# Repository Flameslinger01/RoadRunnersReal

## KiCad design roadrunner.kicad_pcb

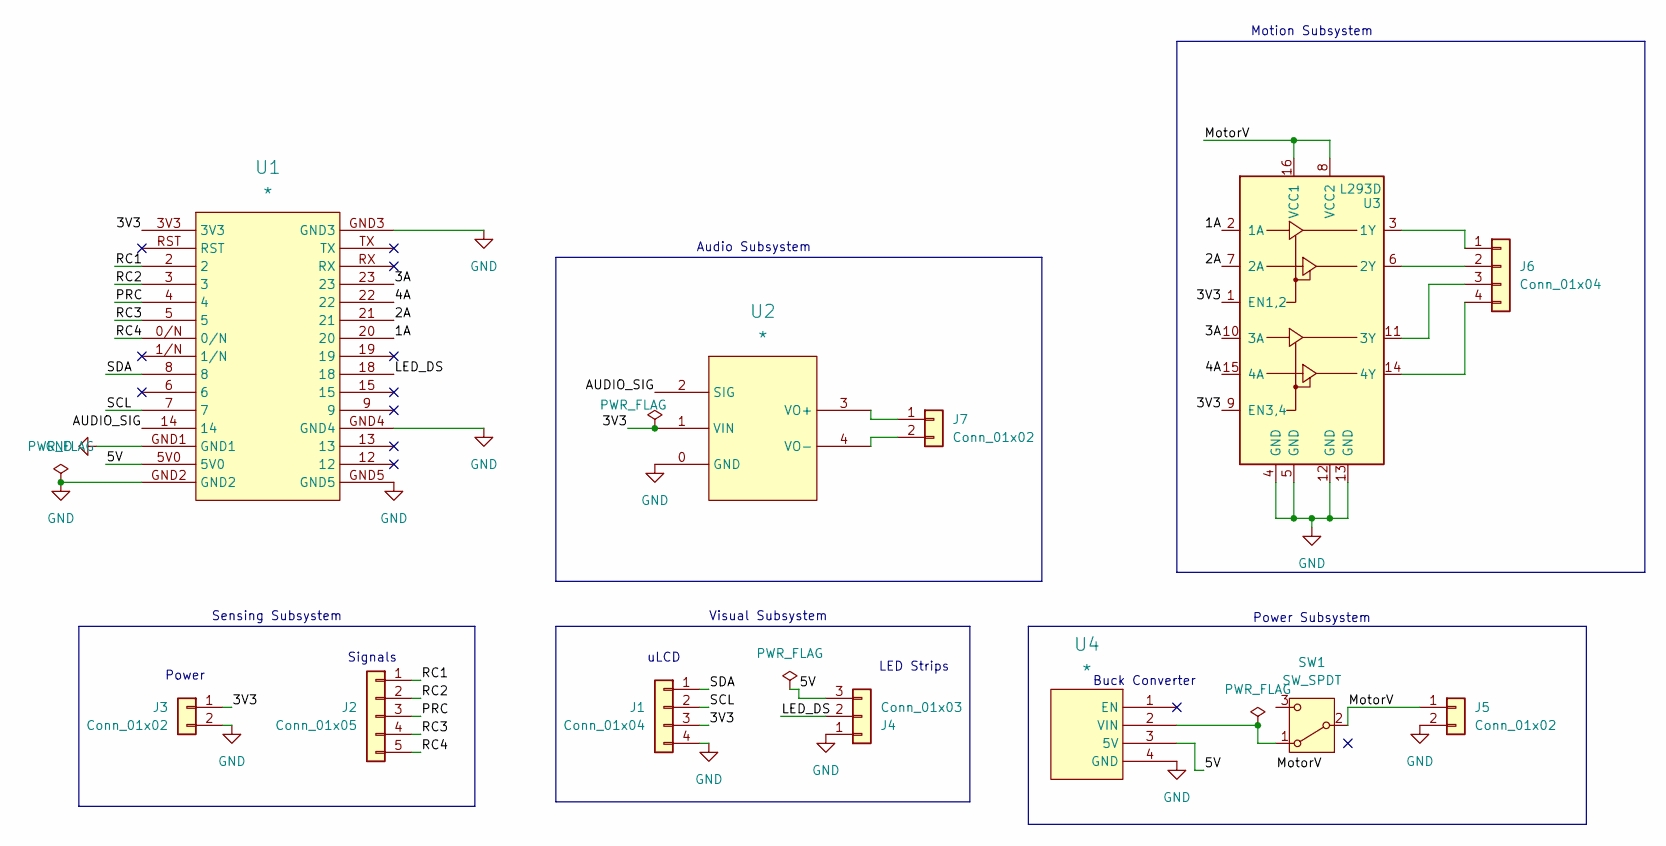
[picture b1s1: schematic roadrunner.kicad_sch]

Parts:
J1, J6: Conn_01x04; JST_XH_B4B-XH-A_1x04_P2.50mm_Vertical
J2: Conn_01x05; JST_XH_B5B-XH-A_1x05_P2.50mm_Vertical
J3, J5, J7: Conn_01x02; JST_XH_B2B-XH-A_1x02_P2.50mm_Vertical
J4: Conn_01x03; JST_XH_B3B-XH-A_1x03_P2.50mm_Vertical
SW1: SW_SPDT; SW_Slide-03_Wuerth-WS-SLTV_10x2.5x6.4_P2.54mm
U1: *; ESP32
U2: *; Adafruit_PAM8904
U3: L293D; DIP-16_W7.62mm
U4: *; ADA4683_MPM3610_BREAKOUT

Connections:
/1A: U1.20, U3.2 (1A)
/2A: U1.21, U3.7 (2A)
/3A: U1.23, U3.10 (3A)
/3V3: J1.3, J3.1, U1.3V3, U2.1 (VIN), U3.1 (EN1,2), U3.9 (EN3,4)
/4A: U1.22, U3.15 (4A)
/5V: J4.3, U1.5V0, U4.3 (5V)
/AUDIO_SIG: U1.14, U2.2 (SIG)
/LED_DS: J4.2, U1.18
/MotorV: J5.1, SW1.2 (B), U3.8 (VCC2), U3.16 (VCC1)
/PRC: J2.3, U1.4
/RC1: J2.1, U1.2
/RC2: J2.2, U1.3
/RC3: J2.4, U1.5
/RC4: J2.5, U1.0/N
/SCL: J1.2, U1.7
/SDA: J1.1, U1.8
GND: J1.4, J3.2, J4.1, J5.2, U1.GND1, U1.GND2, U1.GND3, U1.GND4, U1.GND5, U2.0 (GND), U3.4 (GND), U3.5 (GND), U3.12 (GND), U3.13 (GND), U4.4 (GND)
unnamed: J6.1, U3.3 (1Y)
unnamed: J6.2, U3.6 (2Y)
unnamed: J6.3, U3.11 (3Y)
unnamed: J6.4, U3.14 (4Y)
unnamed: J7.1, U2.3 (VO+)
unnamed: J7.2, U2.4 (VO-)
unnamed: SW1.1 (A), U4.2 (VIN)

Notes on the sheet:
Signals
Buck Converter
Audio Subsystem
uLCD
Power
Visual Subsystem
Power Subsystem
LED Strips
Motion Subsystem
Sensing Subsystem

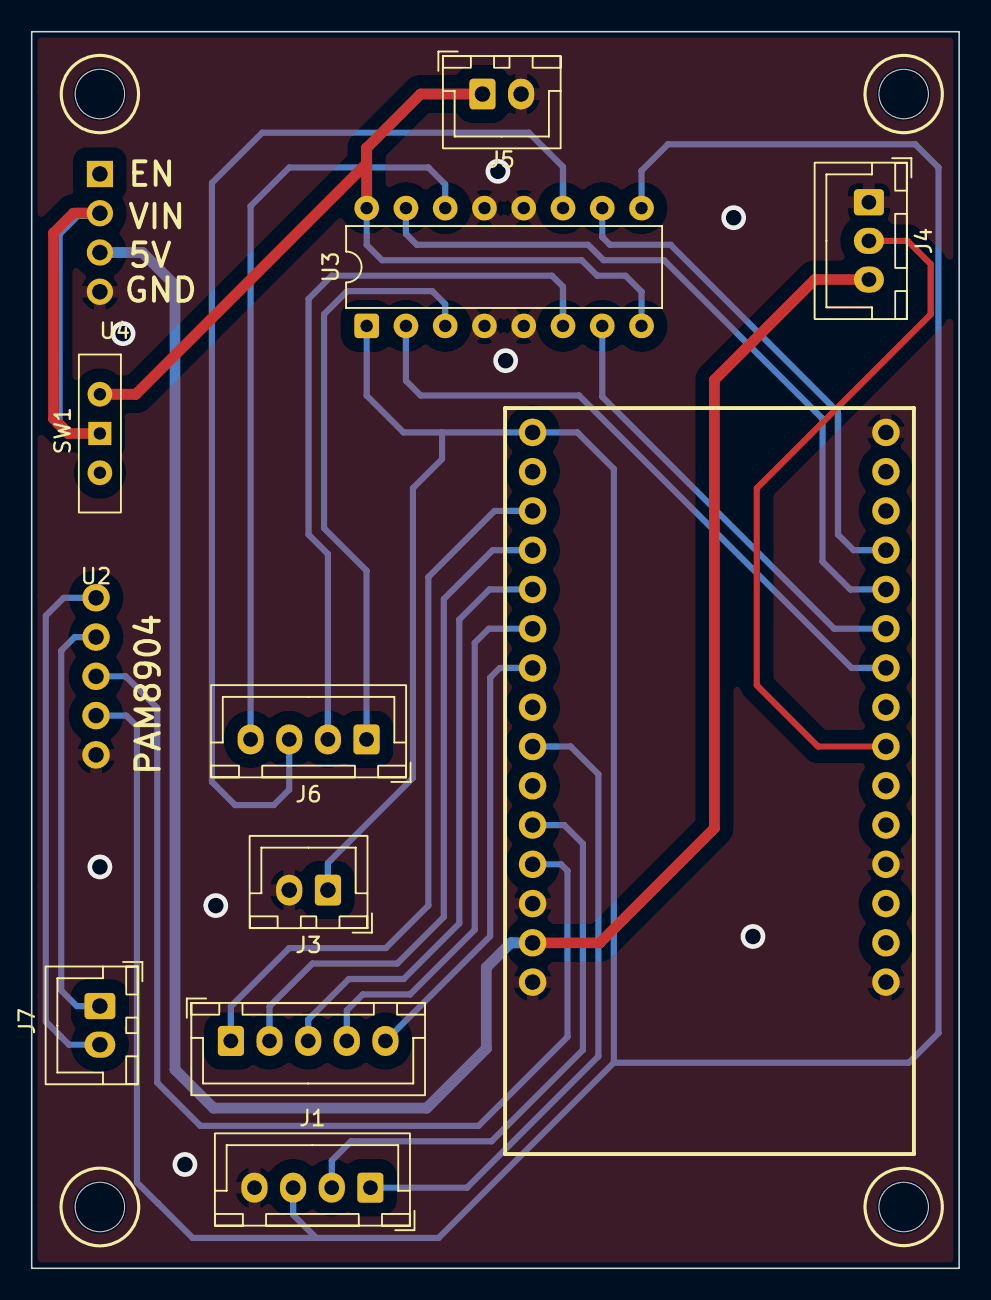
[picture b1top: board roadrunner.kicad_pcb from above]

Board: 2 copper layers, 60.0 x 80.0 mm, 13 parts (0 on the bottom side), 24 nets.

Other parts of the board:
Mounting Hole: MountingHole_3.2mm_M3
